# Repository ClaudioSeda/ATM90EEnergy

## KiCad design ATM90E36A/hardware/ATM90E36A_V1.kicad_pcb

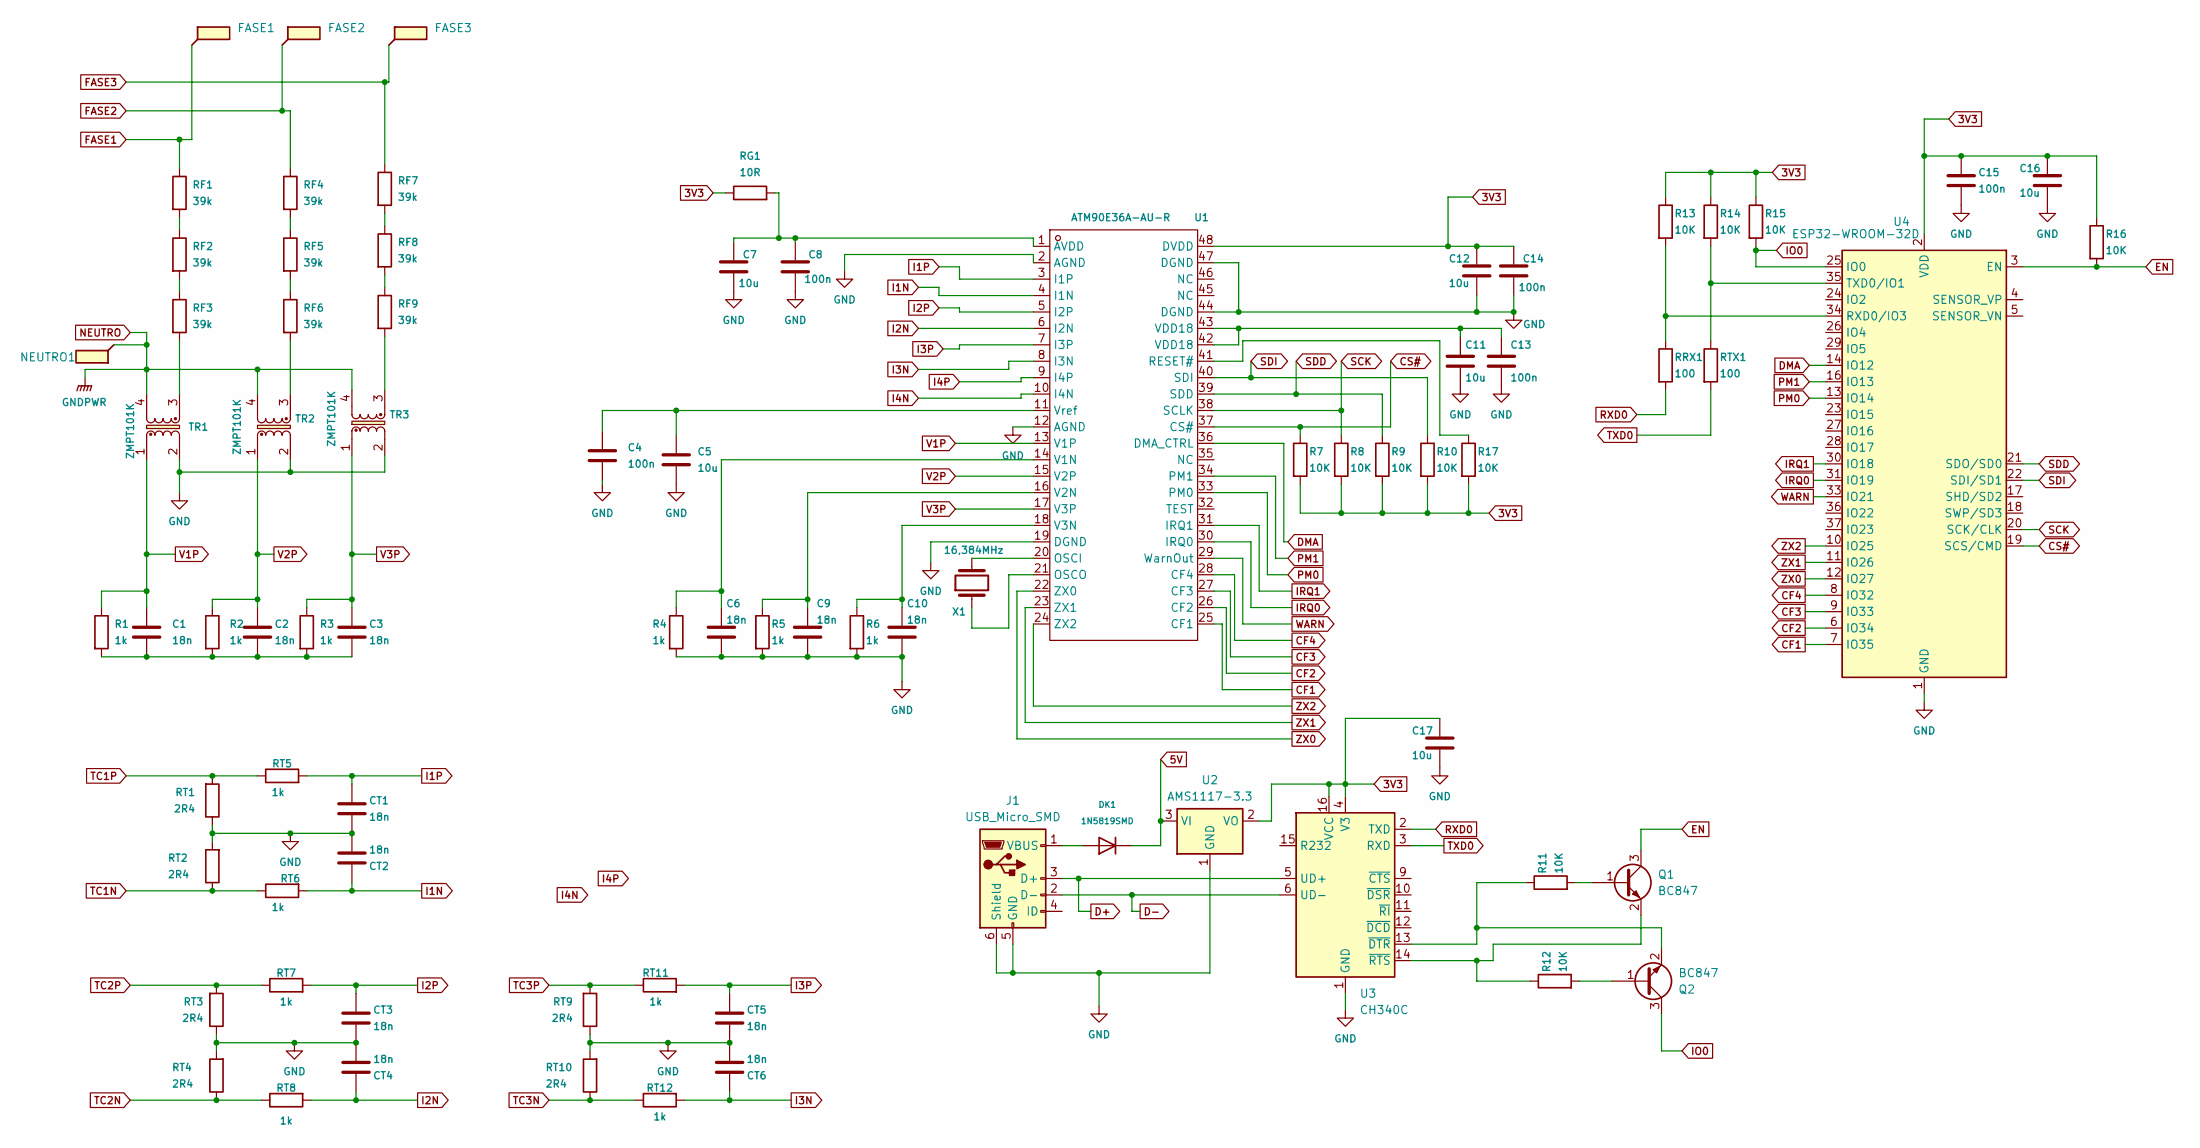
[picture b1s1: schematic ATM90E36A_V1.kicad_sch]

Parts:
C1, C2, C3, C6, C9, C10: 18n; C_0805_2012Metric_Pad1.18x1.45mm_HandSolder
C4, C8, C13, C14, C15: 100n; C_0805_2012Metric_Pad1.18x1.45mm_HandSolder
C5, C7, C11, C12, C16, C17: 10u; C_0805_2012Metric_Pad1.18x1.45mm_HandSolder
CT1, CT2, CT3, CT4, CT5, CT6: 18n; C_0805_2012Metric_Pad1.18x1.45mm_HandSolder
DK1: 1N5819SMD; DIODE_0805
FASE1, FASE2, FASE3: TestPoint_Flag; TestPoint_Plated_Hole_D2.0mm
J1: USB_Micro_SMD; USB_Micro-B_Wuerth_629105150521_CircularHoles
NEUTRO1: TestPoint_Flag; TestPoint_Plated_Hole_D2.0mm
Q1, Q2: BC847; SOT-23
R1, R2, R3, R4, R5, R6: 1k; R_0805_2012Metric_Pad1.20x1.40mm_HandSolder
R7, R8, R9, R10, R11, R12, R13, R14, R15, R16, R17: 10K; R_0805_2012Metric_Pad1.20x1.40mm_HandSolder
RF1, RF2, RF3, RF4, RF5, RF6, RF7, RF8, RF9: 39k; R_1206_3216Metric_Pad1.30x1.75mm_HandSolder
RG1: 10R; R0805
RRX1: 100; R_0805_2012Metric_Pad1.20x1.40mm_HandSolder
RT1, RT2, RT3, RT4, RT9, RT10: 2R4; R_0805_2012Metric_Pad1.20x1.40mm_HandSolder
RT5, RT6, RT7, RT8, RT11, RT12: 1k; R_0805_2012Metric_Pad1.20x1.40mm_HandSolder
RTX1: 100; R_0805_2012Metric_Pad1.20x1.40mm_HandSolder
TR1, TR2, TR3: ZMPT101K; Transformer_Zeming_ZMPT101K
U1: ATM90E36A-AU-R; TQFP-48_7x7mm_P0.5mm; OPERATING VOLTAGE 2.8V~3.6V; MANUFACTURER PART ATM90E36A-AU-R; LCSC PART NAME ATM90E36A 电能计量芯片
U2: AMS1117-3.3; SOT-223-3_TabPin2
U3: CH340C; SOIC-16_3.9x9.9mm_P1.27mm
U4: ESP32-WROOM-32D
X1: 16,384MHz; Crystal_HC49-U_Vertical

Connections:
3V3: C12.1, C14.1, C15.1, C16.1, C17.1, R7.2, R8.2, R9.2, R10.2, R13.1, R14.1, R15.1, R16.1, R17.2, RG1.1, U1.48 (DVDD), U2.2 (VO), U3.4 (V3), U3.16 (VCC), U4.2 (VDD)
5V: DK1.1 (K), U2.3 (VI)
CF1: U1.25 (CF1), U4.7 (IO35)
CF2: U1.26 (CF2), U4.6 (IO34)
CF3: U1.27 (CF3), U4.9 (IO33)
CF4: U1.28 (CF4), U4.8 (IO32)
CS#: R7.1, U1.37 (CS#), U4.19 (SCS/CMD)
D+: J1.3 (D+), U3.5 (UD+)
D-: J1.2 (D-), U3.6 (UD-)
DMA: U1.36 (DMA_CTRL), U4.14 (IO12)
EN: Q1.3 (C), R16.2, U4.3 (EN)
FASE1: FASE1.1, RF1.1
FASE2: FASE2.1, RF4.1
FASE3: FASE3.1, RF7.1
GND: C4.2, C5.2, C6.2, C7.2, C8.2, C9.2, C10.2, C11.2, C12.2, C13.2, C14.2, C15.2, C16.2, C17.2, CT1.2, CT2.2, CT3.2, CT4.2, CT5.2, CT6.2, J1.5 (GND), J1.6 (Shield), R4.2, R5.2, R6.2, RT1.1, RT2.2, RT3.1, RT4.2, RT9.1, RT10.2, TR1.2, TR2.2, TR3.2, U1.2 (AGND), U1.12 (AGND), U1.19 (DGND), U1.44 (DGND), U1.47 (DGND), U2.1 (GND), U3.1 (GND), U4.1 (GND), U4.15 (GND), U4.38 (GND), U4.39 (GND)
I1N: CT2.1, RT6.2, U1.4 (I1N)
I1P: CT1.1, RT5.2, U1.3 (I1P)
I2N: CT4.1, RT8.2, U1.6 (I2N)
I2P: CT3.1, RT7.2, U1.5 (I2P)
I3N: CT6.1, RT12.2, U1.8 (I3N)
I3P: CT5.1, RT11.2, U1.7 (I3P)
I4N: U1.10 (I4N)
I4P: U1.9 (I4P)
IO0: Q2.3 (C), R15.2, U4.25 (IO0)
IRQ0: U1.30 (IRQ0), U4.31 (IO19)
IRQ1: U1.31 (IRQ1), U4.30 (IO18)
NEUTRO: NEUTRO1.1, TR1.4, TR2.4, TR3.4
unnamed: C1.2, C2.2, C3.2, R1.2, R2.2, R3.2
unnamed: C11.1, C13.1, U1.42 (VDD18), U1.43 (VDD18)
unnamed: DK1.2 (A), J1.1 (VBUS)
unnamed: Q1.1 (B), R11.2
unnamed: Q1.2 (E), R12.1, U3.14 (~RTS)
unnamed: Q2.1 (B), R12.2
unnamed: Q2.2 (E), R11.1, U3.13 (~DTR)
unnamed: RF1.2, RF2.1
unnamed: RF2.2, RF3.1
unnamed: RF3.2, TR1.3
unnamed: RF4.2, RF5.1
unnamed: RF5.2, RF6.1
unnamed: RF6.2, TR2.3
unnamed: RF7.2, RF8.1
unnamed: RF8.2, RF9.1
unnamed: RF9.2, TR3.3
unnamed: C7.1, C8.1, RG1.2, U1.1 (AVDD)
unnamed: U1.20 (OSCI), X1.2
unnamed: U1.21 (OSCO), X1.1
unnamed: R17.1, U1.41 (RESET#)
unnamed: C6.1, R4.1, U1.14 (V1N)
unnamed: C9.1, R5.1, U1.16 (V2N)
unnamed: C10.1, R6.1, U1.18 (V3N)
unnamed: C4.1, C5.1, U1.11 (Vref)
unnamed: R13.2, RRX1.1, U4.34 (RXD0/IO3)
unnamed: R14.2, RTX1.1, U4.35 (TXD0/IO1)
PM0: U1.33 (PM0), U4.13 (IO14)
PM1: U1.34 (PM1), U4.16 (IO13)
RXD0: RRX1.2, U3.2 (TXD)
SCK: R8.1, U1.38 (SCLK), U4.20 (SCK/CLK)
SDD: R9.1, U1.39 (SDD), U4.21 (SDO/SD0)
SDI: R10.1, U1.40 (SDI), U4.22 (SDI/SD1)
TC1N: RT2.1, RT6.1
TC1P: RT1.2, RT5.1
TC2N: RT4.1, RT8.1
TC2P: RT3.2, RT7.1
TC3N: RT10.1, RT12.1
TC3P: RT9.2, RT11.1
TXD0: RTX1.2, U3.3 (RXD)
V1P: C1.1, R1.1, TR1.1, U1.13 (V1P)
V2P: C2.1, R2.1, TR2.1, U1.15 (V2P)
V3P: C3.1, R3.1, TR3.1, U1.17 (V3P)
WARN: U1.29 (WarnOut), U4.33 (IO21)
ZX0: U1.22 (ZX0), U4.12 (IO27)
ZX1: U1.23 (ZX1), U4.11 (IO26)
ZX2: U1.24 (ZX2), U4.10 (IO25)

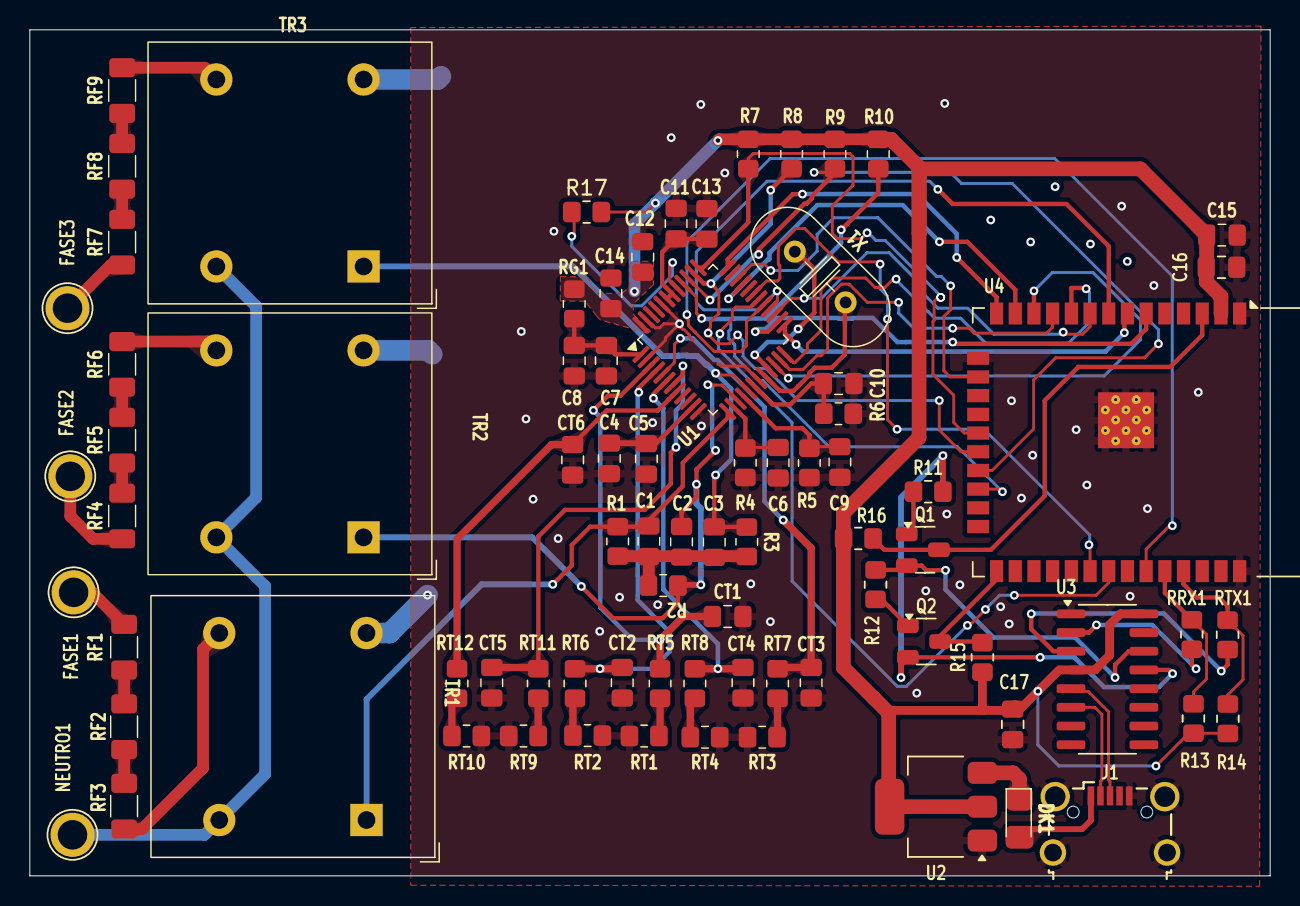
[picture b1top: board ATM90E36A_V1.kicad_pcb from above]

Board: 2 copper layers, 84.2 x 57.5 mm, 80 parts (0 on the bottom side), 71 nets.

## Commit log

2025-05-09 STM32version
2025-05-09 Create STM32F4
2025-05-09 Create ATM90E36A
